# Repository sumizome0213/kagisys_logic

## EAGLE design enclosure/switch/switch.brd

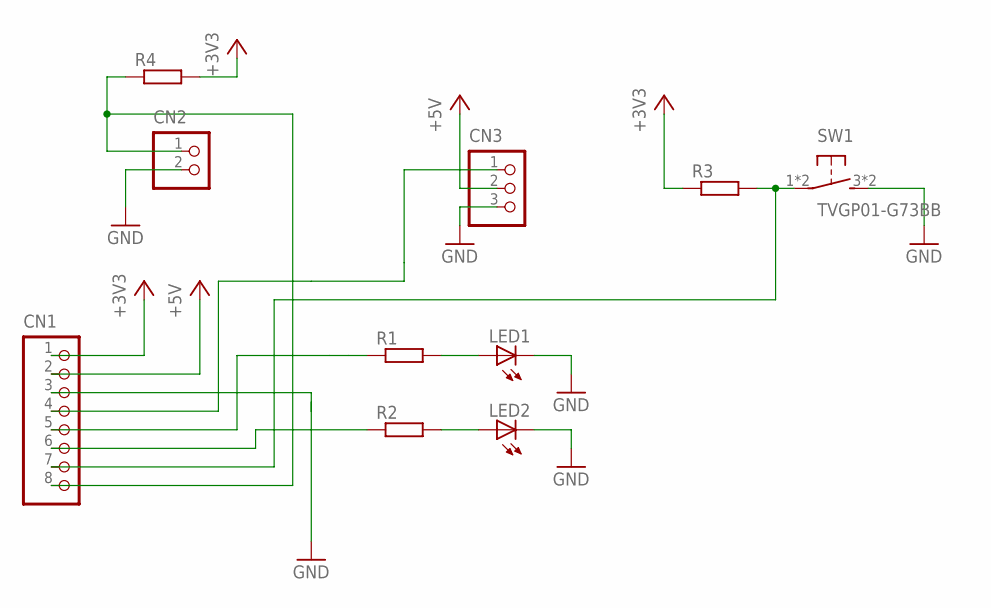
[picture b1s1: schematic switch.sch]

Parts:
CN1: B8B-PH-K-S
CN2: B2B-PH-K-S
CN3: B3B-PH-K-S
LED1, LED2: LED5MM
R1, R2, R3, R4: R-EU_0204/7; 0204/7
SW1: TVGP01-G73BB

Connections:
+3V3: CN1.1, R3.1, R4.2
+5V: CN1.2, CN3.2
GND: CN1.3, CN2.2, CN3.3, LED1.K (C), LED2.K (C), SW1.3 (2), SW1.4 (2)
unnamed: LED1.A, R1.2
unnamed: LED2.A, R2.2
unnamed: CN1.6, R2.1
unnamed: CN1.5, R1.1
unnamed: CN1.7, R3.2, SW1.1, SW1.2 (1)
unnamed: CN1.8, CN2.1, R4.1
unnamed: CN1.4, CN3.1

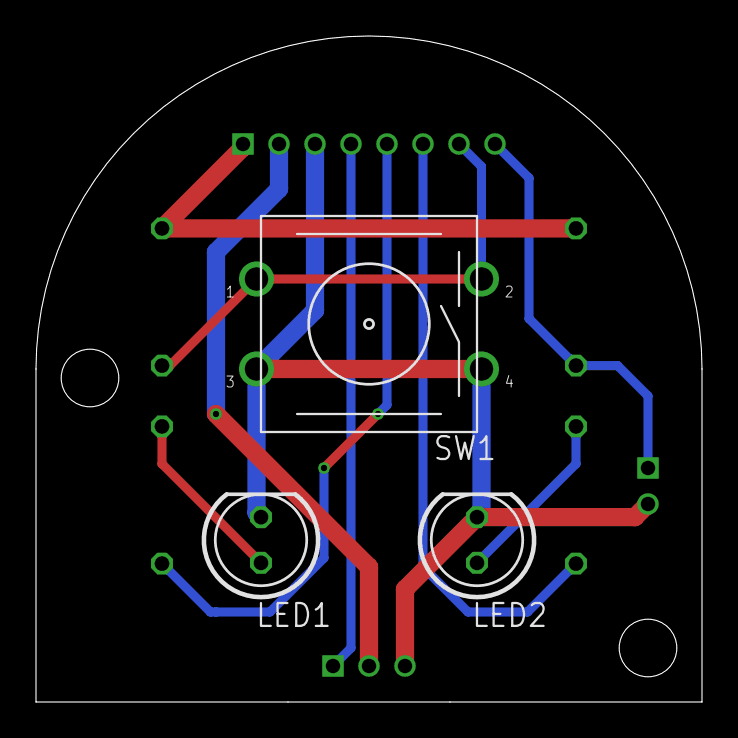
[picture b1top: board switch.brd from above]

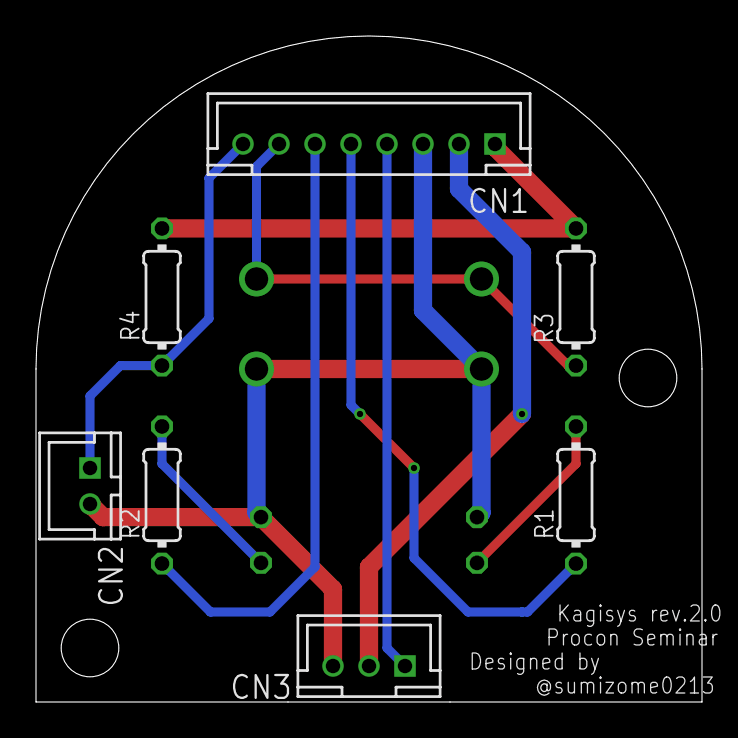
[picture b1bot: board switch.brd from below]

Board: 2 copper layers, 37.0 x 37.0 mm, 10 parts (7 on the bottom side), 10 nets.

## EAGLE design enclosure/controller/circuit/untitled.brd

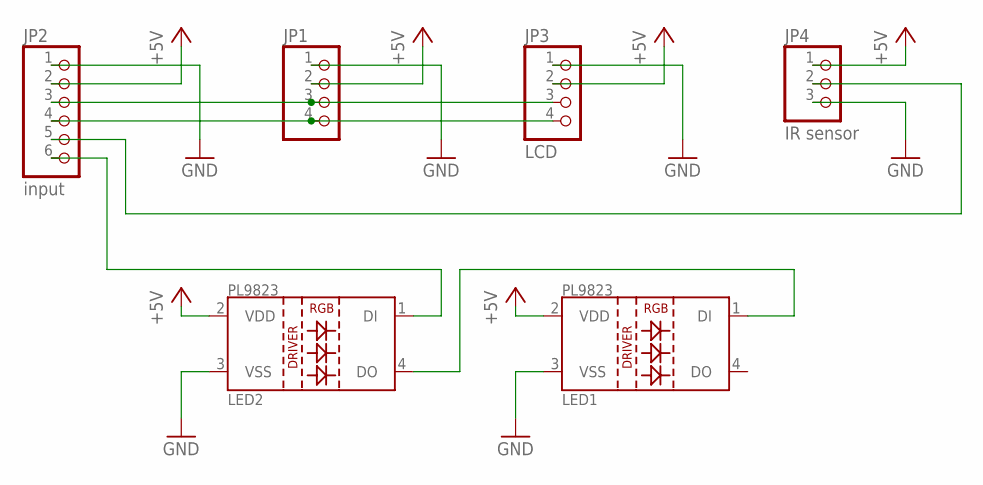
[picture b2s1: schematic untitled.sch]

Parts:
JP1: PINHD-1X4; 1X04
JP2: input; 1X06
JP3: LCD; 1X04
JP4: IR sensor; 1X03
LED1, LED2: LED-PL9823-F5

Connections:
+5V: JP1.2, JP2.2, JP3.2, JP4.1, LED1.2 (VDD), LED2.2 (VDD)
GND: JP1.1, JP2.1, JP3.1, JP4.3, LED1.3 (VSS), LED2.3 (VSS)
unnamed: JP1.3, JP2.3, JP3.3
unnamed: JP2.5, JP4.2
unnamed: JP1.4, JP2.4, JP3.4
unnamed: JP2.6, LED2.1 (DI)
unnamed: LED1.1 (DI), LED2.4 (DO)

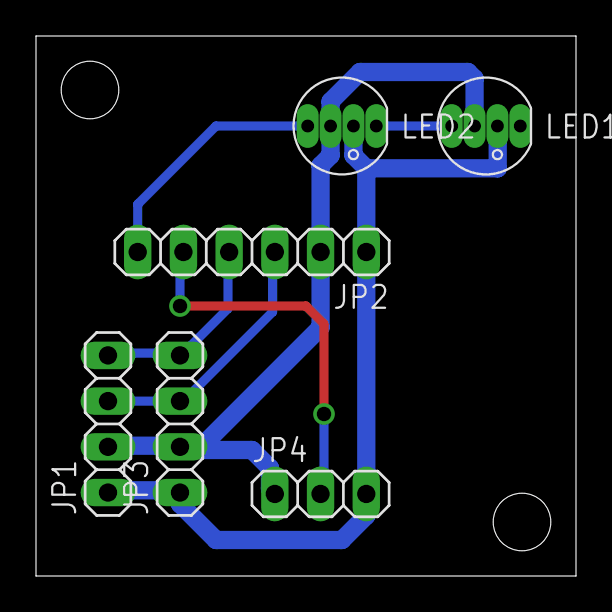
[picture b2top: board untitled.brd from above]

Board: 2 copper layers, 30.0 x 30.0 mm, 6 parts (0 on the bottom side), 7 nets.

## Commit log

2018-03-18 [add] enclosure sketck
2018-07-29 [add] switch基板を作った
2018-07-29 [fix] フォルダの位置を替えた
2018-07-29 [update] brdを作製
2018-09-29 [update] add eagle gitignore
2018-09-30 [update] コネクタをPHにして裏に部品を実装するようにした
2018-09-30 [fix] シルク・位置ずれを解消
2018-09-30 [add] gbrを出力
